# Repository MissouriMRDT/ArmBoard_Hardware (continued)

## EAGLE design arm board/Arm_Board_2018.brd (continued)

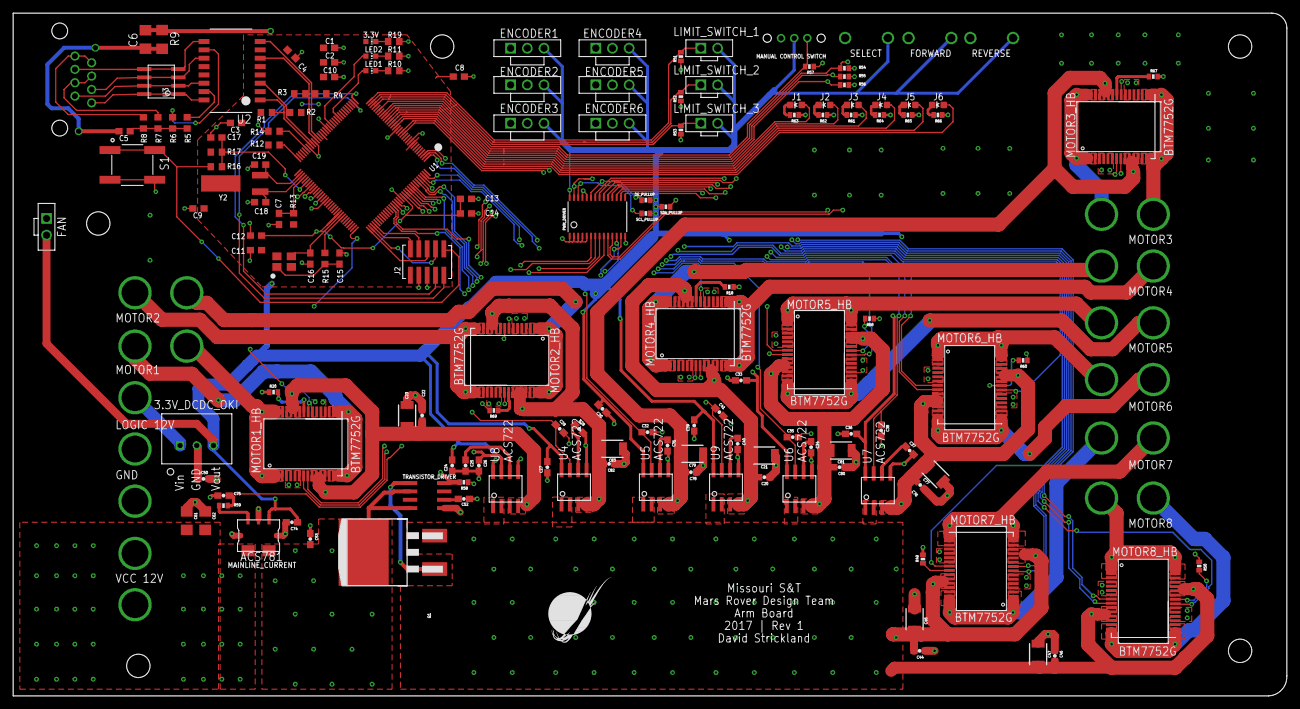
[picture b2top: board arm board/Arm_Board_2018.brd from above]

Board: 4 copper layers, 193.8 x 103.9 mm, 173 parts (0 on the bottom side), 142 nets.

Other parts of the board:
U$5, U$30: MOUNTING_HOLE#6; #6_SCREW

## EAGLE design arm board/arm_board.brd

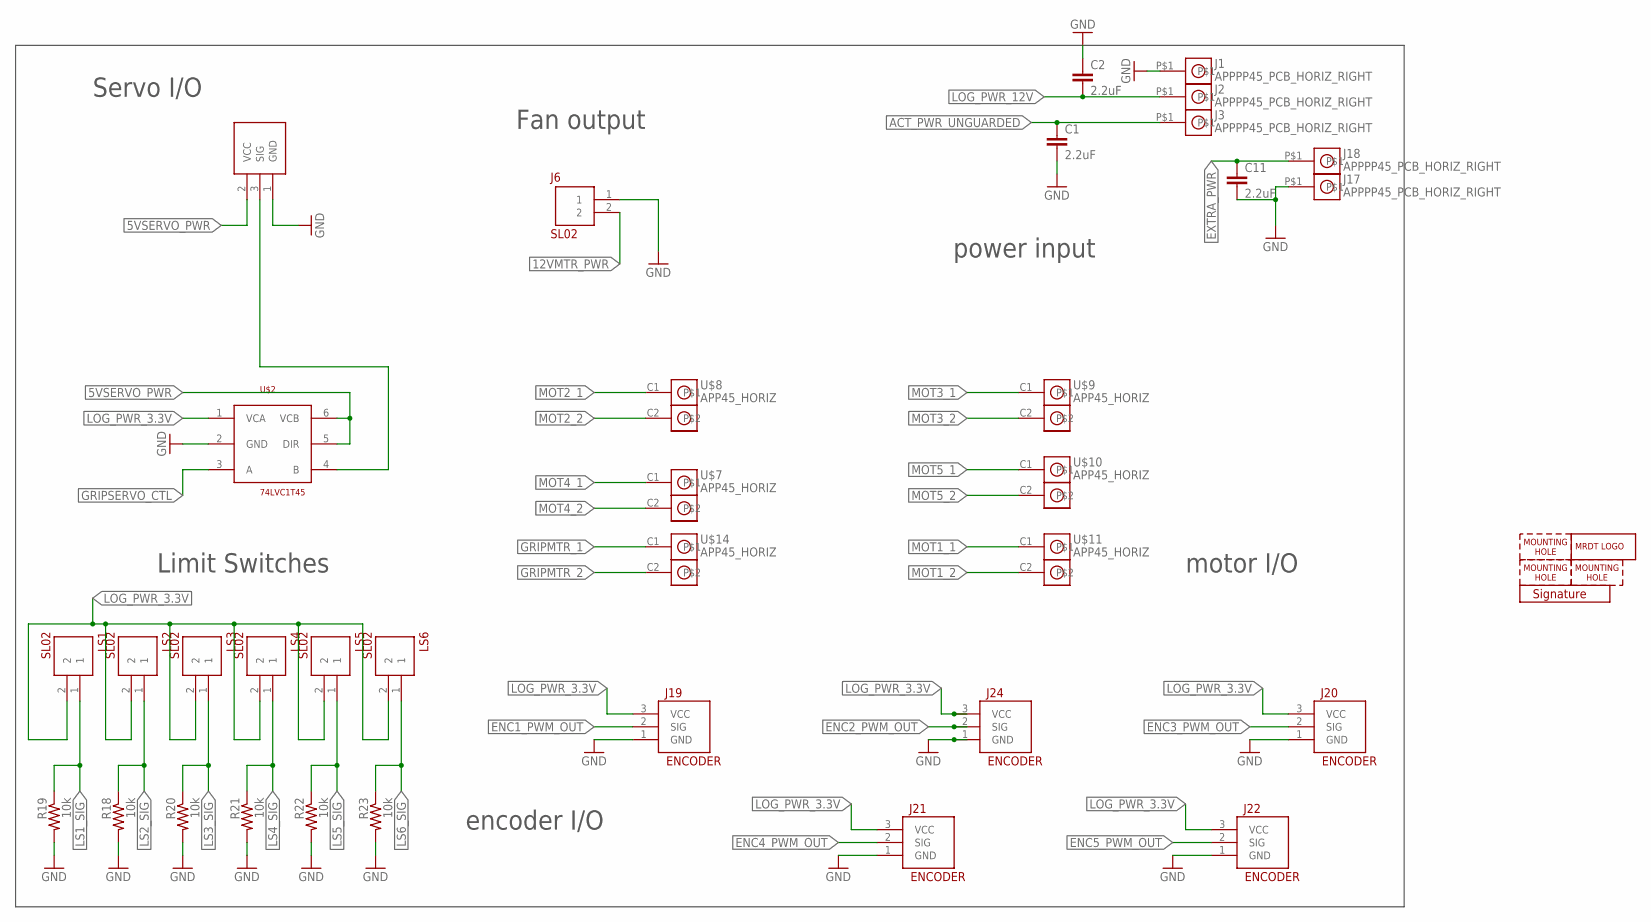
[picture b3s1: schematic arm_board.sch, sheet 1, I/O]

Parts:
C1, C2, C11: 2.2uF; 1206
H1, H2, H4: MOUNTING_HOLE#4; #4_SCREW
J1, J2, J3, J17, J18: APPPP45_PCB_HORIZ_RIGHT; APP45_PCB_HORIZ_RIGHT
J5: SERVOMOLEX_SL_VERT_TH; MOLEX-70543-0002
J6: SL02; MOLEX-70543-0001
J19, J20, J21, J22, J24: ENCODER; MOLEX-70543-0002
LOGO1: MRDT_LOGO
LS1, LS2, LS3, LS4, LS5, LS6: SL02; MOLEX-70543-0001
R18, R19, R20, R21, R22, R23: 10k; 0603-RES
U$2: 74LVC1T45; TSOP-6
U$7, U$8, U$9, U$10, U$11, U$14: APP45_HORIZ; APP45_HORIZ_CONFIG
U$17: SIG

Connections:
5VSERVO_PWR: J5.2 (VCC), U$2.5 (DIR), U$2.6 (VCB); also elsewhere on the board
12VMTR_PWR: J6.2; also elsewhere on the board
ACT_PWR_UNGUARDED: C1.1, J3.P$1; also elsewhere on the board
ENC1_PWM_OUT: J19.2 (SIG); also elsewhere on the board
ENC2_PWM_OUT: J24.2 (SIG); also elsewhere on the board
ENC3_PWM_OUT: J20.2 (SIG); also elsewhere on the board
ENC4_PWM_OUT: J21.2 (SIG); also elsewhere on the board
ENC5_PWM_OUT: J22.2 (SIG); also elsewhere on the board
EXTRA_PWR: C11.1, J18.P$1; also elsewhere on the board
GND: C1.2, C2.1, C11.2, J1.P$1, J5.1 (GND), J6.1, J17.P$1, J19.1 (GND), J20.1 (GND), J21.1 (GND), J22.1 (GND), J24.1 (GND), R18.2, R19.2, R20.2, R21.2, R22.2, R23.2, U$2.2 (GND); also elsewhere on the board
GRIPMTR_1: U$14.C1; also elsewhere on the board
GRIPMTR_2: U$14.C2; also elsewhere on the board
GRIPSERVO_CTL: U$2.3 (A); also elsewhere on the board
LOG_PWR_3.3V: J19.3 (VCC), J20.3 (VCC), J21.3 (VCC), J22.3 (VCC), J24.3 (VCC), LS1.2, LS2.2, LS3.2, LS4.2, LS5.2, LS6.2, U$2.1 (VCA); also elsewhere on the board
LOG_PWR_12V: C2.2, J2.P$1; also elsewhere on the board
LS1_SIG: LS1.1, R19.1; also elsewhere on the board
LS3_SIG: LS3.1, R20.1; also elsewhere on the board
MOT1_1: U$11.C1; also elsewhere on the board
MOT1_2: U$11.C2; also elsewhere on the board
MOT2_1: U$8.C1; also elsewhere on the board
MOT2_2: U$8.C2; also elsewhere on the board
MOT3_1: U$9.C1; also elsewhere on the board
MOT3_2: U$9.C2; also elsewhere on the board
MOT4_1: U$7.C1; also elsewhere on the board
MOT4_2: U$7.C2; also elsewhere on the board
MOT5_1: U$10.C1; also elsewhere on the board
MOT5_2: U$10.C2; also elsewhere on the board
unnamed: J5.3 (SIG), U$2.4 (B)

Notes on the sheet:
power input
motor I/O
encoder I/O
Servo I/O
Fan output
Limit Switches

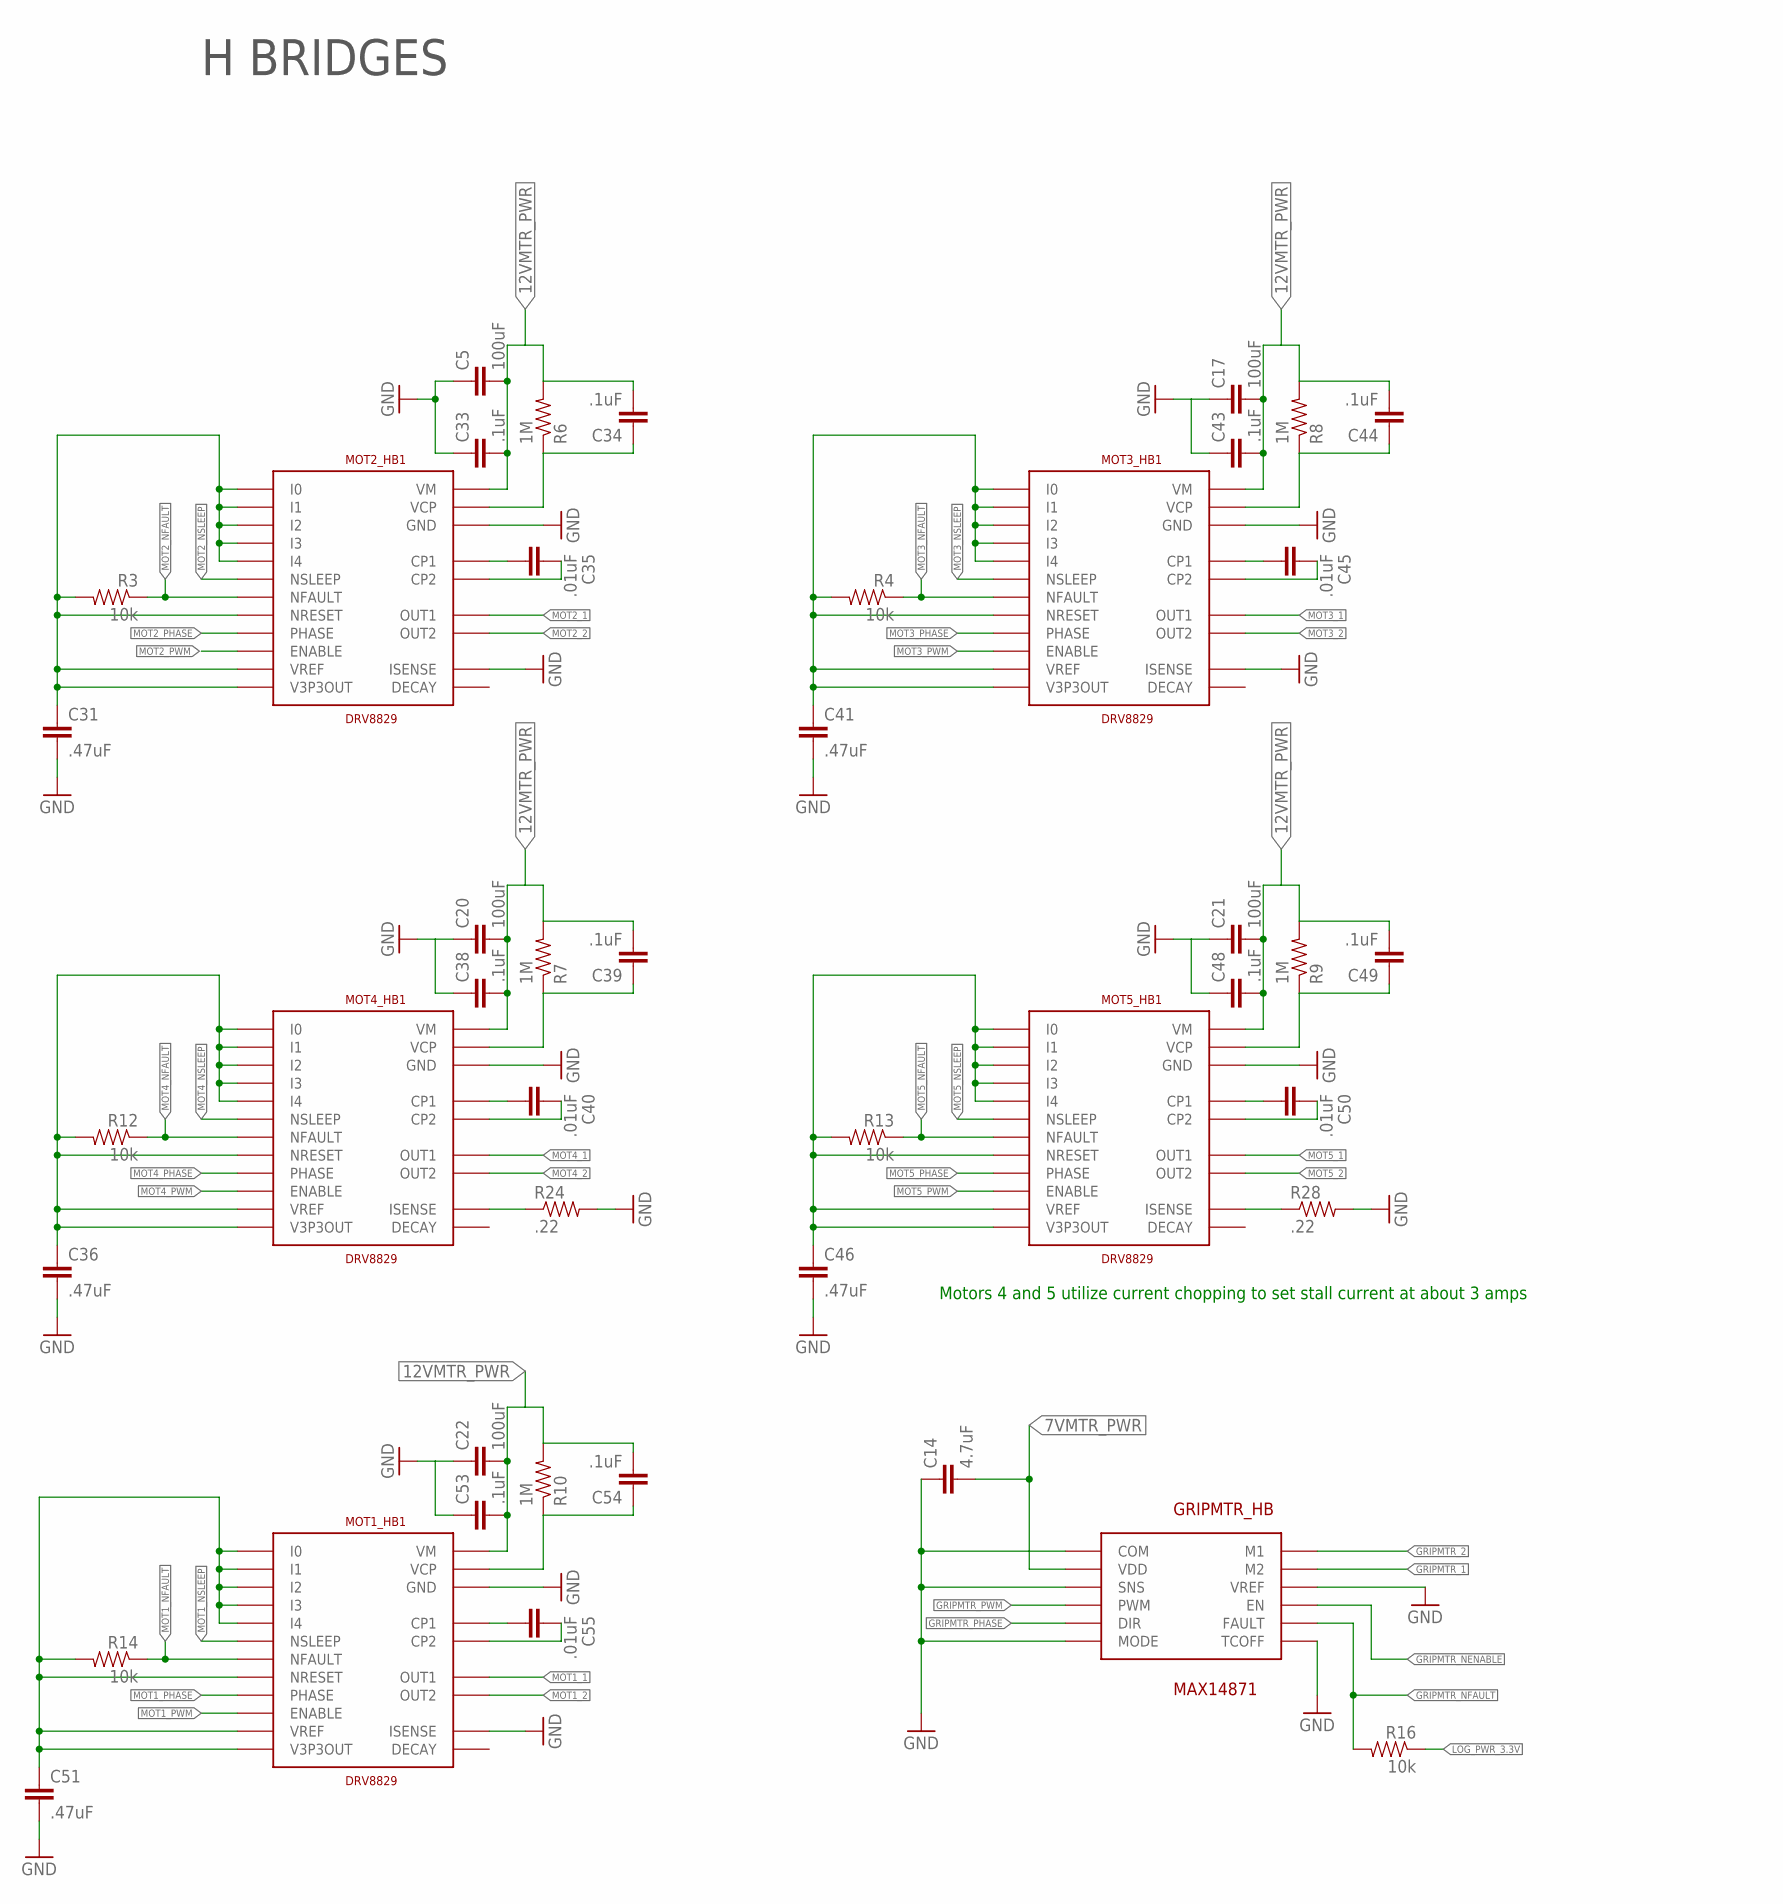
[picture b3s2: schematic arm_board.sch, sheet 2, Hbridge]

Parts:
C5, C17, C20, C21, C22: 100uF; 1210
C14: 4.7uF; 1206
C31, C36, C41, C46, C51: .47uF; 0603-CAP
C33, C34, C38, C39, C43, C44, C48, C49, C53, C54: .1uF; 0603-CAP
C35, C40, C45, C50, C55: .01uF; 0603-CAP
GRIPMTR_HB: MAX14871; TSSOP-16
MOT1_HB1, MOT2_HB1, MOT3_HB1, MOT4_HB1, MOT5_HB1: DRV8829; TSSOP28-GROUNDPAD
R3, R4, R12, R13, R14, R16: 10k; 0603-RES
R6, R7, R8, R9, R10: 1M; 0603-RES
R24, R28: .22; R2512

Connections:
7VMTR_PWR: C14.2, GRIPMTR_HB.4 (VDD), GRIPMTR_HB.13 (VDD); also elsewhere on the board
12VMTR_PWR: C5.2, C17.2, C20.2, C21.2, C22.2, C33.2, C34.2, C38.2, C39.2, C43.2, C44.2, C48.2, C49.2, C53.2, C54.2, MOT1_HB1.4 (VM), MOT1_HB1.11 (VM), MOT2_HB1.4 (VM), MOT2_HB1.11 (VM), MOT3_HB1.4 (VM), MOT3_HB1.11 (VM), MOT4_HB1.4 (VM), MOT4_HB1.11 (VM), MOT5_HB1.4 (VM), MOT5_HB1.11 (VM), R6.2, R7.2, R8.2, R9.2, R10.2; also elsewhere on the board
GND: C5.1, C14.1, C17.1, C20.1, C21.1, C22.1, C31.2, C33.1, C36.2, C38.1, C41.2, C43.1, C46.2, C48.1, C51.2, C53.1, GRIPMTR_HB.1 (COM), GRIPMTR_HB.5 (SNS), GRIPMTR_HB.8 (MODE), GRIPMTR_HB.9 (TCOFF), GRIPMTR_HB.12 (VREF), GRIPMTR_HB.16 (COM), MOT1_HB1.6 (ISENSE), MOT1_HB1.9 (ISENSE), MOT1_HB1.14 (GND), MOT1_HB1.28 (GND), MOT1_HB1.29 (GND), MOT2_HB1.6 (ISENSE), MOT2_HB1.9 (ISENSE), MOT2_HB1.14 (GND), MOT2_HB1.28 (GND), MOT2_HB1.29 (GND), MOT3_HB1.6 (ISENSE), MOT3_HB1.9 (ISENSE), MOT3_HB1.14 (GND), MOT3_HB1.28 (GND), MOT3_HB1.29 (GND), MOT4_HB1.14 (GND), MOT4_HB1.28 (GND), MOT4_HB1.29 (GND), MOT5_HB1.14 (GND), MOT5_HB1.28 (GND), MOT5_HB1.29 (GND), R24.2, R28.2; also elsewhere on the board
GRIPMTR_1: GRIPMTR_HB.14 (M2), GRIPMTR_HB.15 (M2); also elsewhere on the board
GRIPMTR_2: GRIPMTR_HB.2 (M1), GRIPMTR_HB.3 (M1); also elsewhere on the board
GRIPMTR_NENABLE: GRIPMTR_HB.11 (EN); also elsewhere on the board
GRIPMTR_NFAULT: GRIPMTR_HB.10 (FAULT), R16.2; also elsewhere on the board
GRIPMTR_PHASE: GRIPMTR_HB.7 (DIR); also elsewhere on the board
GRIPMTR_PWM: GRIPMTR_HB.6 (PWM); also elsewhere on the board
HB_3.3_OUTPUT5: C31.1, MOT2_HB1.12 (VREF), MOT2_HB1.13 (VREF), MOT2_HB1.15 (V3P3OUT), MOT2_HB1.16 (NRESET), MOT2_HB1.23 (I0), MOT2_HB1.24 (I1), MOT2_HB1.25 (I2), MOT2_HB1.26 (I3), MOT2_HB1.27 (I4), R3.2
HB_3.3_OUTPUT6: C36.1, MOT4_HB1.12 (VREF), MOT4_HB1.13 (VREF), MOT4_HB1.15 (V3P3OUT), MOT4_HB1.16 (NRESET), MOT4_HB1.23 (I0), MOT4_HB1.24 (I1), MOT4_HB1.25 (I2), MOT4_HB1.26 (I3), MOT4_HB1.27 (I4), R12.2
HB_3.3_OUTPUT7: C41.1, MOT3_HB1.12 (VREF), MOT3_HB1.13 (VREF), MOT3_HB1.15 (V3P3OUT), MOT3_HB1.16 (NRESET), MOT3_HB1.23 (I0), MOT3_HB1.24 (I1), MOT3_HB1.25 (I2), MOT3_HB1.26 (I3), MOT3_HB1.27 (I4), R4.2
HB_3.3_OUTPUT8: C46.1, MOT5_HB1.12 (VREF), MOT5_HB1.13 (VREF), MOT5_HB1.15 (V3P3OUT), MOT5_HB1.16 (NRESET), MOT5_HB1.23 (I0), MOT5_HB1.24 (I1), MOT5_HB1.25 (I2), MOT5_HB1.26 (I3), MOT5_HB1.27 (I4), R13.2
HB_3.3_OUTPUT9: C51.1, MOT1_HB1.12 (VREF), MOT1_HB1.13 (VREF), MOT1_HB1.15 (V3P3OUT), MOT1_HB1.16 (NRESET), MOT1_HB1.23 (I0), MOT1_HB1.24 (I1), MOT1_HB1.25 (I2), MOT1_HB1.26 (I3), MOT1_HB1.27 (I4), R14.2
LOG_PWR_3.3V: R16.1; also elsewhere on the board
MOT1_1: MOT1_HB1.5 (OUT1), MOT1_HB1.10 (OUT1); also elsewhere on the board
MOT1_2: MOT1_HB1.7 (OUT2), MOT1_HB1.8 (OUT2); also elsewhere on the board
MOT1_NFAULT: MOT1_HB1.18 (NFAULT), R14.1; also elsewhere on the board
MOT1_NSLEEP: MOT1_HB1.17 (NSLEEP); also elsewhere on the board
MOT1_PHASE: MOT1_HB1.20 (PHASE); also elsewhere on the board
MOT1_PWM: MOT1_HB1.21 (ENABLE); also elsewhere on the board
MOT2_1: MOT2_HB1.5 (OUT1), MOT2_HB1.10 (OUT1); also elsewhere on the board
MOT2_2: MOT2_HB1.7 (OUT2), MOT2_HB1.8 (OUT2); also elsewhere on the board
MOT2_NFAULT: MOT2_HB1.18 (NFAULT), R3.1; also elsewhere on the board
MOT2_NSLEEP: MOT2_HB1.17 (NSLEEP); also elsewhere on the board
MOT2_PHASE: MOT2_HB1.20 (PHASE); also elsewhere on the board
MOT2_PWM: MOT2_HB1.21 (ENABLE); also elsewhere on the board
MOT3_1: MOT3_HB1.5 (OUT1), MOT3_HB1.10 (OUT1); also elsewhere on the board
MOT3_2: MOT3_HB1.7 (OUT2), MOT3_HB1.8 (OUT2); also elsewhere on the board
MOT3_NFAULT: MOT3_HB1.18 (NFAULT), R4.1; also elsewhere on the board
MOT3_NSLEEP: MOT3_HB1.17 (NSLEEP); also elsewhere on the board
MOT3_PHASE: MOT3_HB1.20 (PHASE); also elsewhere on the board
MOT3_PWM: MOT3_HB1.21 (ENABLE); also elsewhere on the board
MOT4_1: MOT4_HB1.5 (OUT1), MOT4_HB1.10 (OUT1); also elsewhere on the board
MOT4_2: MOT4_HB1.7 (OUT2), MOT4_HB1.8 (OUT2); also elsewhere on the board
MOT4_NFAULT: MOT4_HB1.18 (NFAULT), R12.1; also elsewhere on the board
MOT4_NSLEEP: MOT4_HB1.17 (NSLEEP); also elsewhere on the board
MOT4_PHASE: MOT4_HB1.20 (PHASE); also elsewhere on the board
MOT4_PWM: MOT4_HB1.21 (ENABLE); also elsewhere on the board
MOT5_1: MOT5_HB1.5 (OUT1), MOT5_HB1.10 (OUT1); also elsewhere on the board
MOT5_2: MOT5_HB1.7 (OUT2), MOT5_HB1.8 (OUT2); also elsewhere on the board
MOT5_NFAULT: MOT5_HB1.18 (NFAULT), R13.1; also elsewhere on the board
MOT5_NSLEEP: MOT5_HB1.17 (NSLEEP); also elsewhere on the board
MOT5_PHASE: MOT5_HB1.20 (PHASE); also elsewhere on the board
MOT5_PWM: MOT5_HB1.21 (ENABLE); also elsewhere on the board
unnamed: MOT4_HB1.6 (ISENSE), MOT4_HB1.9 (ISENSE), R24.1
unnamed: MOT5_HB1.6 (ISENSE), MOT5_HB1.9 (ISENSE), R28.1
unnamed: C34.1, MOT2_HB1.3 (VCP), R6.1
unnamed: C35.2, MOT2_HB1.1 (CP1)
unnamed: C35.1, MOT2_HB1.2 (CP2)
unnamed: C39.1, MOT4_HB1.3 (VCP), R7.1
unnamed: C40.2, MOT4_HB1.1 (CP1)
unnamed: C40.1, MOT4_HB1.2 (CP2)
unnamed: C44.1, MOT3_HB1.3 (VCP), R8.1
unnamed: C45.2, MOT3_HB1.1 (CP1)
unnamed: C45.1, MOT3_HB1.2 (CP2)
unnamed: C49.1, MOT5_HB1.3 (VCP), R9.1
unnamed: C50.2, MOT5_HB1.1 (CP1)
unnamed: C50.1, MOT5_HB1.2 (CP2)
unnamed: C54.1, MOT1_HB1.3 (VCP), R10.1
unnamed: C55.2, MOT1_HB1.1 (CP1)
unnamed: C55.1, MOT1_HB1.2 (CP2)

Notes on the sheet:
H BRIDGES
Motors 4 and 5 utilize current chopping to set stall current at about 3 amps

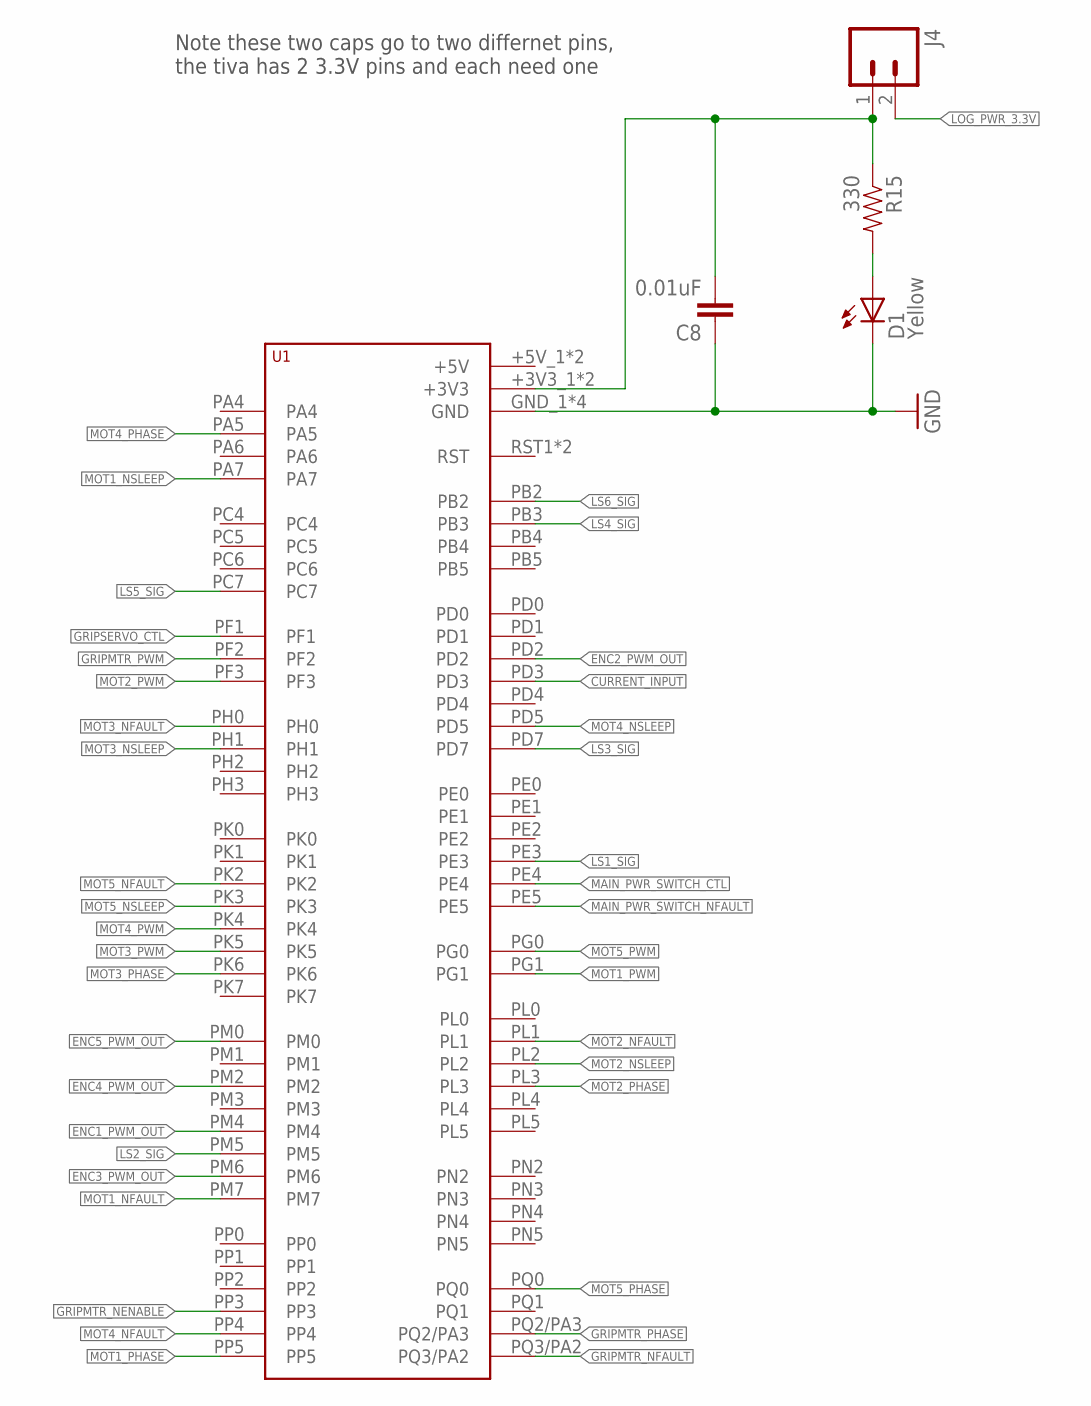
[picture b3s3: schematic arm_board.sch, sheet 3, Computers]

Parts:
C8: 0.01uF; 0603-CAP
D1: Yellow; LED-1206
J4: M02PTH; 1X02
R15: 330; 0603-RES@1
U1: TIVA-1294; TIVA-C-CONNECTED

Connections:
CURRENT_INPUT: U1.PD3; also elsewhere on the board
ENC1_PWM_OUT: U1.PM4; also elsewhere on the board
ENC2_PWM_OUT: U1.PD2; also elsewhere on the board
ENC3_PWM_OUT: U1.PM6; also elsewhere on the board
ENC4_PWM_OUT: U1.PM2; also elsewhere on the board
ENC5_PWM_OUT: U1.PM0; also elsewhere on the board
GND: C8.1, D1.C, U1.GND_1 (GND), U1.GND_2 (GND), U1.GND_3 (GND), U1.GND_4 (GND); also elsewhere on the board
GRIPMTR_NENABLE: U1.PP3; also elsewhere on the board
GRIPMTR_NFAULT: U1.PQ3/PA2; also elsewhere on the board
GRIPMTR_PHASE: U1.PQ2/PA3; also elsewhere on the board
GRIPMTR_PWM: U1.PF2; also elsewhere on the board
GRIPSERVO_CTL: U1.PF1; also elsewhere on the board
LOG_PWR_3.3V: J4.2; also elsewhere on the board
LS1_SIG: U1.PE3; also elsewhere on the board
LS3_SIG: U1.PD7; also elsewhere on the board
MAIN_PWR_SWITCH_CTL: U1.PE4; also elsewhere on the board
MOT1_NFAULT: U1.PM7; also elsewhere on the board
MOT1_NSLEEP: U1.PA7; also elsewhere on the board
MOT1_PHASE: U1.PP5; also elsewhere on the board
MOT1_PWM: U1.PG1; also elsewhere on the board
MOT2_NFAULT: U1.PL1; also elsewhere on the board
MOT2_NSLEEP: U1.PL2; also elsewhere on the board
MOT2_PHASE: U1.PL3; also elsewhere on the board
MOT2_PWM: U1.PF3; also elsewhere on the board
MOT3_NFAULT: U1.PH0; also elsewhere on the board
MOT3_NSLEEP: U1.PH1; also elsewhere on the board
MOT3_PHASE: U1.PK6; also elsewhere on the board
MOT3_PWM: U1.PK5; also elsewhere on the board
MOT4_NFAULT: U1.PP4; also elsewhere on the board
MOT4_NSLEEP: U1.PD5; also elsewhere on the board
MOT4_PHASE: U1.PA5; also elsewhere on the board
MOT4_PWM: U1.PK4; also elsewhere on the board
MOT5_NFAULT: U1.PK2; also elsewhere on the board
MOT5_NSLEEP: U1.PK3; also elsewhere on the board
MOT5_PHASE: U1.PQ0; also elsewhere on the board
MOT5_PWM: U1.PG0; also elsewhere on the board
unnamed: D1.A, R15.2
unnamed: C8.2, J4.1, R15.1, U1.+3V3_1 (+3V3), U1.+3V3_2 (+3V3)

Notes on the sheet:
Note these two caps go to two differnet pins, the tiva has 2 3.3V pins and each need one

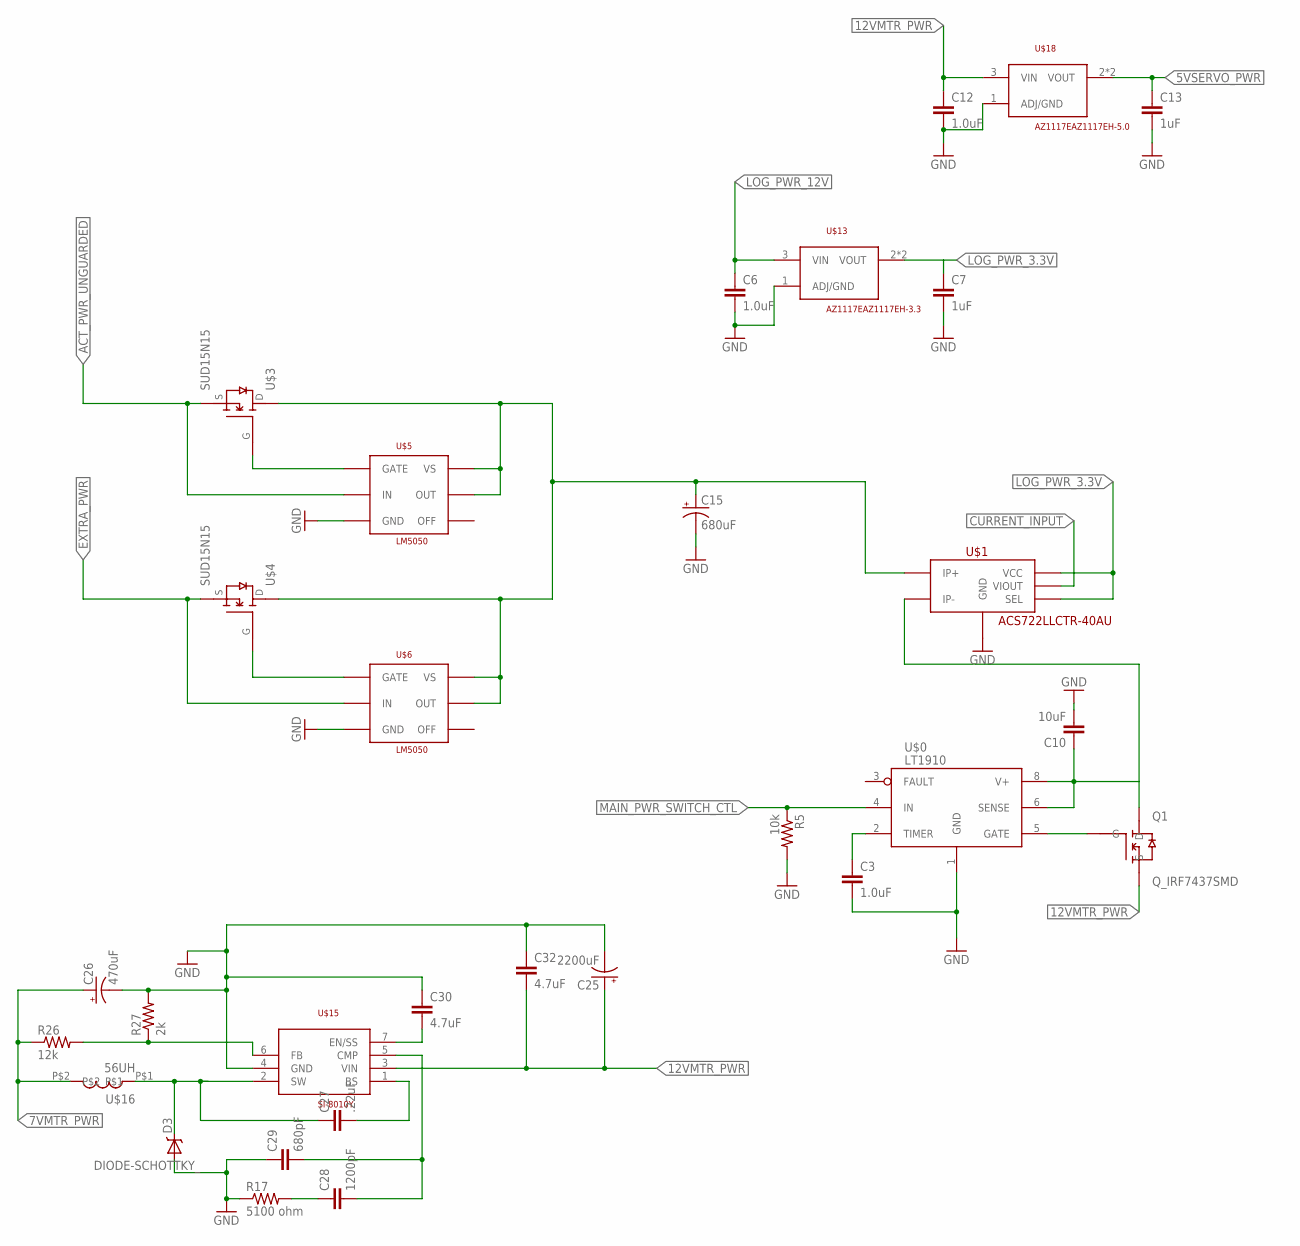
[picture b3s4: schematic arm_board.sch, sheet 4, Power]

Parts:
C3, C6, C12: 1.0uF; 0603-CAP
C7, C13: 1uF; 0603-CAP
C10: 10uF; 0805
C15: 680uF; PANASONIC_G
C25: 2200uF; C_16MM
C26: 470uF; PANASONIC_H13
C27: .22uF; 1206
C28: 1200pF; 1206
C29: 680pF; 1206
C30, C32: 4.7uF; 1206
D3: DIODE-SCHOTTKY_; SMA-DIODE
Q1: Q_IRF7437SMD; D2PACK
R5: 10k; 0603-RES
R17: 5100 ohm; 0603-RES
R26: 12k; 0603-RES
R27: 2k; 0603-RES
U$0: LT1910; SO8
U$1: ACS722LLCTR-40AU; SOIC8
U$3, U$4: SUD15N15; TO252
U$5, U$6: LM5050; TSOT23-6
U$13: AZ1117EAZ1117EH-3.3; SOT223
U$15: SI-8010Y; TO-220-7
U$16: 56UH; .5*.5_SMD
U$18: AZ1117EAZ1117EH-5.0; SOT223

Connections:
5VSERVO_PWR: C13.1, U$18.2 (VOUT), U$18.4 (VOUT); also elsewhere on the board
7VMTR_PWR: C26.+, R26.1, U$16.P$2; also elsewhere on the board
12VMTR_PWR: C12.1, C25.+, C32.2, Q1.2 (S), U$15.3 (VIN), U$18.3 (VIN); also elsewhere on the board
$N3: C10.1, Q1.TAB (D), U$0.6 (SENSE), U$0.8 (V+), U$1.3 (IP-), U$1.4 (IP-)
ACT_PWR_UNGUARDED: U$3.2 (S), U$5.4 (IN); also elsewhere on the board
CURRENT_INPUT: U$1.7 (VIOUT); also elsewhere on the board
DUAL_PWR: C15.+, U$1.1 (IP+), U$1.2 (IP+), U$3.3 (D), U$4.3 (D), U$5.1 (VS), U$5.6 (OUT), U$6.1 (VS), U$6.6 (OUT)
EXTRA_PWR: U$4.2 (S), U$6.4 (IN); also elsewhere on the board
GND: C3.2, C6.2, C7.2, C10.2, C12.2, C13.2, C15.-, C25.GND (-), C26.-, C29.1, C30.1, C32.1, D3.A, R5.2, R17.1, R27.2, U$0.1 (GND), U$1.5 (GND), U$5.2 (GND), U$6.2 (GND), U$13.1 (ADJ/GND), U$15.4 (GND), U$18.1 (ADJ/GND); also elsewhere on the board
LOG_PWR_3.3V: C7.1, U$1.6 (SEL), U$1.8 (VCC), U$13.2 (VOUT), U$13.4 (VOUT); also elsewhere on the board
LOG_PWR_12V: C6.1, U$13.3 (VIN); also elsewhere on the board
MAIN_PWR_SWITCH_CTL: R5.1, U$0.4 (IN); also elsewhere on the board
unnamed: C3.1, U$0.2 (TIMER)
unnamed: Q1.1 (G), U$0.5 (GATE)
unnamed: U$3.1 (G), U$5.5 (GATE)
unnamed: C30.2, U$15.7 (EN/SS)
unnamed: R26.2, R27.1, U$15.6 (FB)
unnamed: U$4.1 (G), U$6.5 (GATE)
unnamed: C28.1, R17.2
unnamed: C28.2, C29.2, U$15.5 (CMP)
unnamed: C27.2, U$15.1 (BS)
unnamed: C27.1, D3.C, U$15.2 (SW), U$16.P$1

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
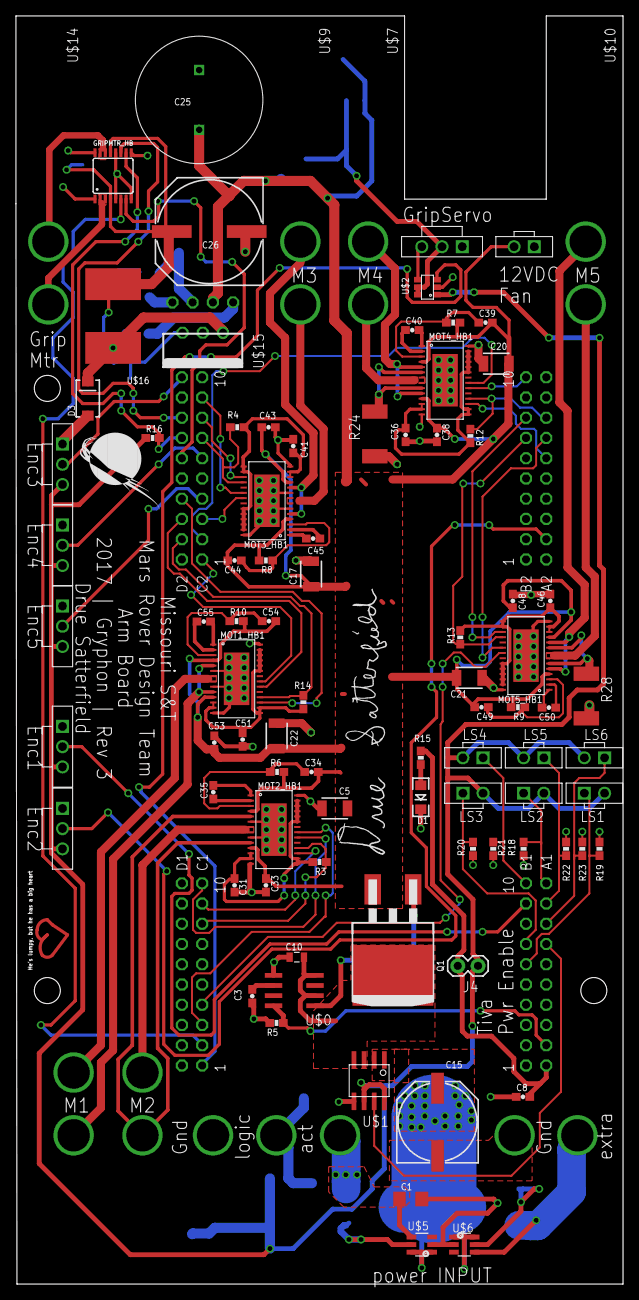
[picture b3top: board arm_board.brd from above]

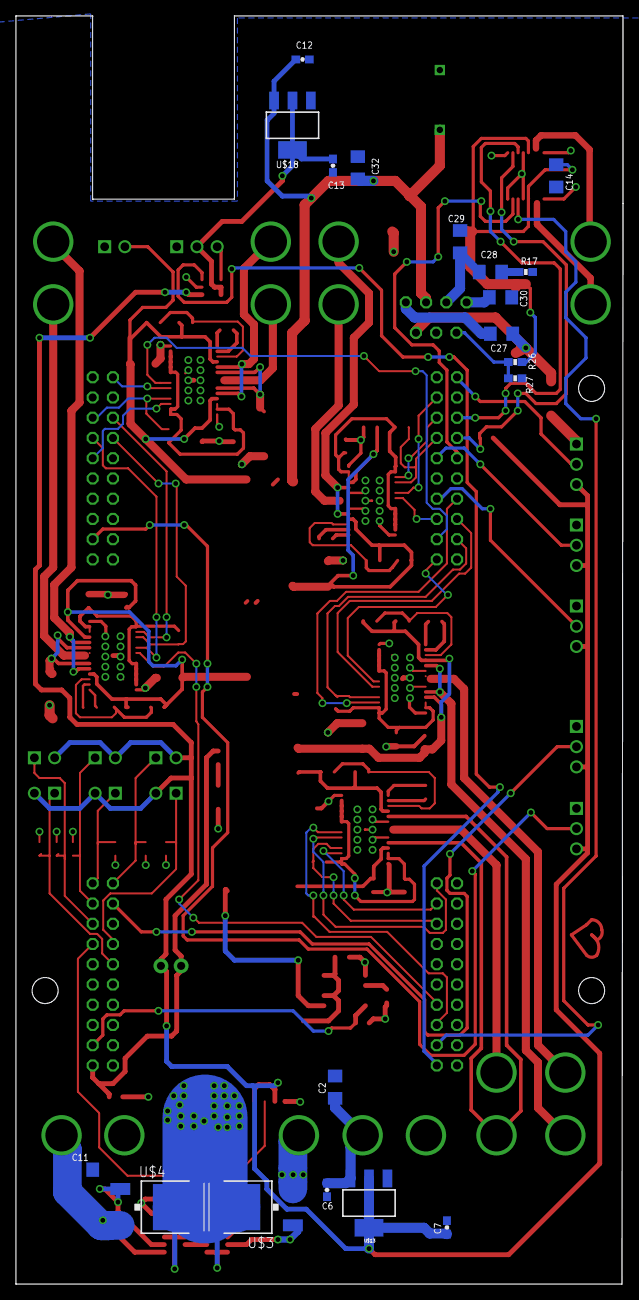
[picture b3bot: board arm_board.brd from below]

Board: 2 copper layers, 76.2 x 159.1 mm, 119 parts (19 on the bottom side), 95 nets.

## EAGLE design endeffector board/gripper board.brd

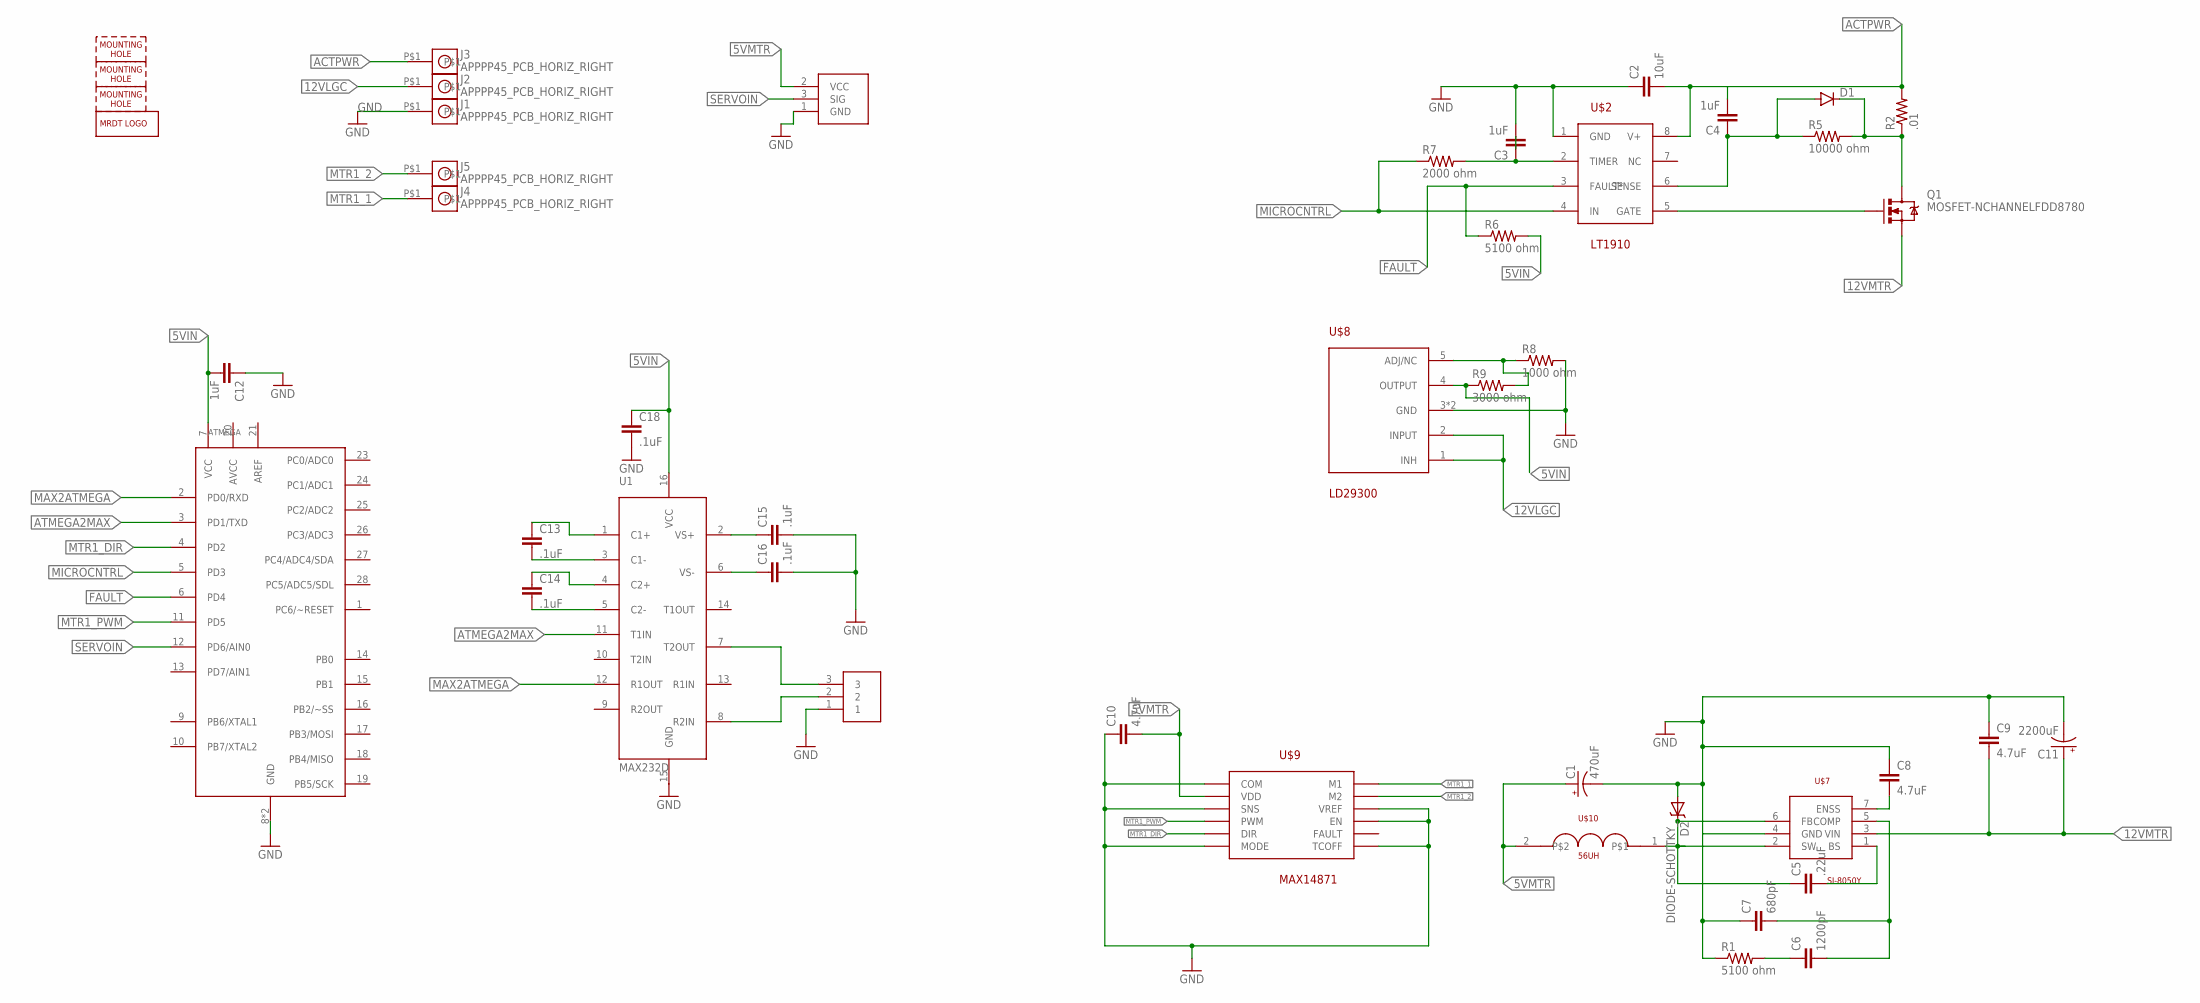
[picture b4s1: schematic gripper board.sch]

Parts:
ATMEGA: Q_ATMEGA328P; DIP28
C1: 470uF; PANASONIC_H13
C2: 10uF; 0603-CAP
C3, C4, C12: 1uF; 0603-CAP
C5: .22uF; 1206
C6: 1200pF; 1206
C7: 680pF; 1206
C8, C9, C10: 4.7uF; 1206
C11: 2200uF; C_16MM
C13, C14, C15, C16, C18: .1uF; 0805
D1: DIODESMA; SMA-DIODE
D2: DIODE-SCHOTTKY_; SMA-DIODE
H1, H2, H3: MOUNTING_HOLE#4; #4_SCREW
J1, J2, J3, J4, J5: APPPP45_PCB_HORIZ_RIGHT; APP45_PCB_HORIZ_RIGHT
J6: SL03; MOLEX-70543-0002
LOGO1: MRDT_LOGO
Q1: MOSFET-NCHANNELFDD8780; DPAK
R1, R6: 5100 ohm; 0603-RES
R2: .01; 1206
R5: 10000 ohm; 0603-RES
R7: 2000 ohm; 0603-RES
R8: 1000 ohm; 0603-RES
R9: 3000 ohm; 0603-RES
U1: MAX232D; SOIC16
U$1: SERVOMOLEX_SL_VERT_TH; MOLEX-70543-0002
U$2: LT1910; SOIC8
U$7: SI-8050Y; TO-220-7
U$8: LD29300; P2PAK
U$9: MAX14871; TSSOP-16
U$10: 56UH; 1210

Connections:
5VIN: ATMEGA.7 (VCC), C12.2, C18.1, R6.2, R9.1, U1.16 (VCC), U$8.4 (OUTPUT)
5VMTR: C1.+, C10.2, U$1.2 (VCC), U$9.4 (VDD), U$9.13 (VDD), U$10.2
12VLGC: J2.P$1, U$8.1 (INH), U$8.2 (INPUT)
12VMTR: C9.2, C11.+, Q1.3 (S), U$7.3 (VIN)
ACTPWR: C2.2, C4.2, J3.P$1, R2.2, U$2.8 (V+)
ATMEGA2MAX: ATMEGA.3 (PD1/TXD), U1.11 (T1IN)
FAULT: ATMEGA.6 (PD4), R6.1, U$2.3 (FAULT*)
GND: ATMEGA.8 (GND), ATMEGA.22 (GND), C1.-, C2.1, C3.2, C7.1, C8.1, C9.1, C10.1, C11.GND (-), C12.1, C15.2, C16.2, C18.2, D2.A, J1.P$1, J6.1, R1.1, R8.2, U1.15 (GND), U$1.1 (GND), U$2.1 (GND), U$7.4 (GND), U$8.3 (GND), U$8.P$1 (GND), U$9.1 (COM), U$9.5 (SNS), U$9.8 (MODE), U$9.9 (TCOFF), U$9.11 (EN), U$9.12 (VREF), U$9.16 (COM)
MAX2ATMEGA: ATMEGA.2 (PD0/RXD), U1.12 (R1OUT)
MICROCNTRL: ATMEGA.5 (PD3), R7.1, U$2.4 (IN)
MTR1_1: J4.P$1, U$9.2 (M1), U$9.3 (M1)
MTR1_2: J5.P$1, U$9.14 (M2), U$9.15 (M2)
MTR1_DIR: ATMEGA.4 (PD2), U$9.7 (DIR)
MTR1_PWM: ATMEGA.11 (PD5), U$9.6 (PWM)
unnamed: C3.1, R7.2, U$2.2 (TIMER)
unnamed: R8.1, R9.2, U$8.5 (ADJ/NC)
unnamed: C13.2, U1.3 (C1-)
unnamed: C6.1, R1.2
unnamed: C4.1, D1.A, R5.1, U$2.6 (SENSE)
unnamed: Q1.1 (G), U$2.5 (GATE)
unnamed: C8.2, U$7.7 (ENSS)
unnamed: D1.C, Q1.4 (D), R2.1, R5.2
unnamed: C6.2, C7.2, U$7.5 (COMP)
unnamed: C5.2, U$7.1 (BS)
unnamed: C14.2, U1.5 (C2-)
unnamed: C14.1, U1.4 (C2+)
unnamed: C13.1, U1.1 (C1+)
unnamed: C15.1, U1.2 (VS+)
unnamed: C16.1, U1.6 (VS-)
unnamed: J6.3, U1.7 (T2OUT)
unnamed: J6.2, U1.8 (R2IN)
unnamed: C5.1, D2.C, U$7.2 (SW), U$7.6 (FB), U$10.1
SERVOIN: ATMEGA.12 (PD6/AIN0), U$1.3 (SIG)
